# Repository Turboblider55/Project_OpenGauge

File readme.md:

<div align="center">

# 🛰️ OpenGauge

### Moduláris járműtelemetria és kijelző OBD-II-n keresztül

*Kétegységes, vezeték nélküli műszerfal valós idejű járműdiagnosztikához.*

</div>

---

*<p align="center">Illusztráció (koncepció): a jármű CAN-buszától a műszerfalra szerelhető, kerek kijelzőig.</p>*

---

## 📖 Áttekintés

Az **OpenGauge** egy BSc-szakdolgozati projekt: a jármű diagnosztikai adatainak beolvasását és megjelenítését két külön egységre bontja, amelyeket vezeték nélküli kapcsolat köt össze. Egyetlen, kijelzővel ellátott OBD-II dongle helyett két, a feladatára készült egység készül:

- **OBD-egység:** az OBD-II csatlakozóba dugott kis panel, amely a jármű CAN-buszáról olvassa a diagnosztikai adatokat, és a járműről kapja a tápfeszültségét.
- **Kijelzőegység:** a műszerfalra vagy a szellőzőrácsra szerelhető, kerek érintőkijelzős egység, amely vezeték nélkül kapja az adatokat, és animált műszereket jelenít meg. Akkumulátorról és USB-ről is működik.

A projekt része a két NYÁK megtervezése, legyártatása és üzembe helyezése, a beágyazott szoftver, a felhasználói felület és a 3D nyomtatott házak is.

A projekt nyíltan dokumentálja a tervezési hibákat is (hibanapló a `docs/` mappában), mert a felismert hibák és javításuk a fejlesztési folyamat része, és tanulságot adnak a következő verzióhoz.

---

## 🧭 Rendszerfelépítés

```
┌────────────────────────┐
│     JÁRMŰ (ECU-k)      │
│   CAN-H / CAN-L busz   │
└──────────┬─────────────┘
           │  OBD-II (J1962), ISO 15765-4
           ▼
┌────────────────────────────────────────────┐
│              OBD-EGYSÉG                    │
│  ESP32-C3-WROOM-02                         │
│  CAN-illesztő (SN65HVD23x), TWAI           │
│  Buck-áramkör (TPS54302): 12 V → 3,3 V     │
│  Bemeneti védelem (D8 SS34, D4 SMAJ24A)    │
└────────────────────┬───────────────────────┘
                     │  ESP-NOW (2,4 GHz, fix csatorna)
                     ▼
┌────────────────────────────────────────────────────┐
│              KIJELZŐEGYSÉG                         │
│  ESP32-S3-WROOM-1-N8R8 (8 MB PSRAM)                │
│  LVGL 9, QSPI kijelző-meghajtás                    │
│  Waveshare 1,85" kerek kijelző (ST77916, 360×360)  │
│  Érintő: CST816S (I²C)                             │
│  Táp: USB-C + 1S LiPo (TP4056, tápútválasztás)     │
└────────────────────────────────────────────────────┘
```

---

## ✨ Főbb jellemzők

**Hardver**
- Két egyedi, négyrétegű NYÁK (JLCPCB gyártás és szerelés).
- OBD-egység: szinkron buck, fordított polaritás elleni védelem, TVS, CAN-illesztő, ESP32-C3 modul, natív USB.
- Kijelzőegység: ESP32-S3 PSRAM-mal, USB-C és LiPo táp, töltő és tápútválasztás, 3,3 V-os LDO.

**Szoftver**
- OBD-II Mode 01 PID-ek ciklikus lekérdezése (fordulatszám, sebesség, hűtővíz, fojtószelep, akkumulátorfeszültség), a protokoll automatikus felismerésével (250/500 kbit/s, 11/29 bites azonosító).
- Többkeretes (ISO-TP) válaszok kezelése, VIN-lekérdezés.
- ESP-NOW telemetria egyszerű, verziózott bináris csomagokkal és sorszám-ellenőrzéssel.
- LVGL-alapú kerek műszerfal, folyamatos mutatómozgás a ritkább mérési adatok között.

**Opcionális bővítések**
- Alvó üzemmód, gyújtásra ébredéssel.
- BLE: médiavezérlés iOS-en (Apple Media Service) és Androidon (HID).
- Hibakódok **olvasása**.

---

## 📁 Tárolószerkezet

```
OpenGauge/
├── hardware/               # KiCad-projektek, gyártófájlok, BOM
├── firmware/
│   ├── components/         # közös komponensek (og_protocol, og_obd, og_common)
│   ├── obd_node/           # OBD-egység (ESP32-C3)
│   ├── display_node/       # kijelzőegység (ESP32-S3)
│   └── tools/
│       ├── ecu_sim/        # ESP32-S2: tesztadó és ECU-szimulátor
│       └── host_test/      # PC-s egységtesztek
├── mechanical/             # 3D nyomtatott házak (STEP/STL)
├── docs/
│   ├── fejlesztesi_naplo.xlsx   # hibák, változtatások, tervezési döntések
│   ├── 00_kepek/
│   ├── 01_projekt_bemutatas/
│   ├── 02_szoftver/
│   └── 03_hardver/
├── LICENSE
└── README.md
```

A lábkiosztások, alkatrészlisták és méretezések a `docs/03_hardver/` mappában vannak, egyetlen helyen, hogy ne legyen ellentmondás a dokumentumok között.

---

## 🛠️ Első lépések

**Előfeltételek**
- [ESP-IDF](https://docs.espressif.com/projects/esp-idf/en/latest/esp32/get-started/) 5.x (Windowson ESP-IDF Tools Installer vagy a VS Code Espressif-bővítmény)
- [KiCad](https://www.kicad.org/) a hardvertervek megnyitásához
- CMake és C++ fordító a PC-s tesztekhez

**PC-s tesztek (ESP-IDF nélkül)**
```bash
cd firmware
cmake -S tools/host_test -B build_host
cmake --build build_host
ctest --test-dir build_host --output-on-failure
```

**Fordítás és feltöltés**
```bash
# OBD-egység (ESP32-C3)
cd firmware/obd_node
idf.py set-target esp32c3
idf.py -p COM5 flash monitor

# Kijelzőegység (ESP32-S3)
cd ../display_node
idf.py set-target esp32s3
idf.py -p COM7 flash monitor
```
Két panel naplója egyszerre is figyelhető: mindkettő külön soros porton jelenik meg, külön terminálokból.

---

## 📜 Licenc és felelősségkizárás

A projekt **MIT licenc** alatt áll, a részletek a [`LICENSE`](LICENSE) fájlban találhatók.

> ⚠️ **Gépjárművi biztonsági figyelmeztetés**
> Az OpenGauge **csak olvasó** diagnosztikai eszköz. Kizárólag szabványos OBD-II diagnosztikai kéréseket küld (olvasó szolgáltatások: Mode 01 és Mode 09, tervezetten Mode 03), a válaszokat megjeleníti, de **nem ír, nem töröl és nem módosít** semmit a járműben: nem törli a hibakódokat, nem küld vezérlő- vagy beavatkozó keretet. Oktatási és diagnosztikai megjelenítési célra készült, **nem** tanúsított gépjárművi biztonsági, kibocsátás-ellenőrző vagy vezérlőeszköz. A használat saját felelősségre történik, a szerzők nem vállalnak felelősséget a jármű meghibásodásáért, elektromos károkért vagy balesetekért. Járműre csatlakoztatás előtt győződj meg a megfelelő védelemről és az OBD-II csatlakozó szabályos használatáról.

---

<div align="center">

**OpenGauge**: BSc-szakdolgozati projekt.

</div>

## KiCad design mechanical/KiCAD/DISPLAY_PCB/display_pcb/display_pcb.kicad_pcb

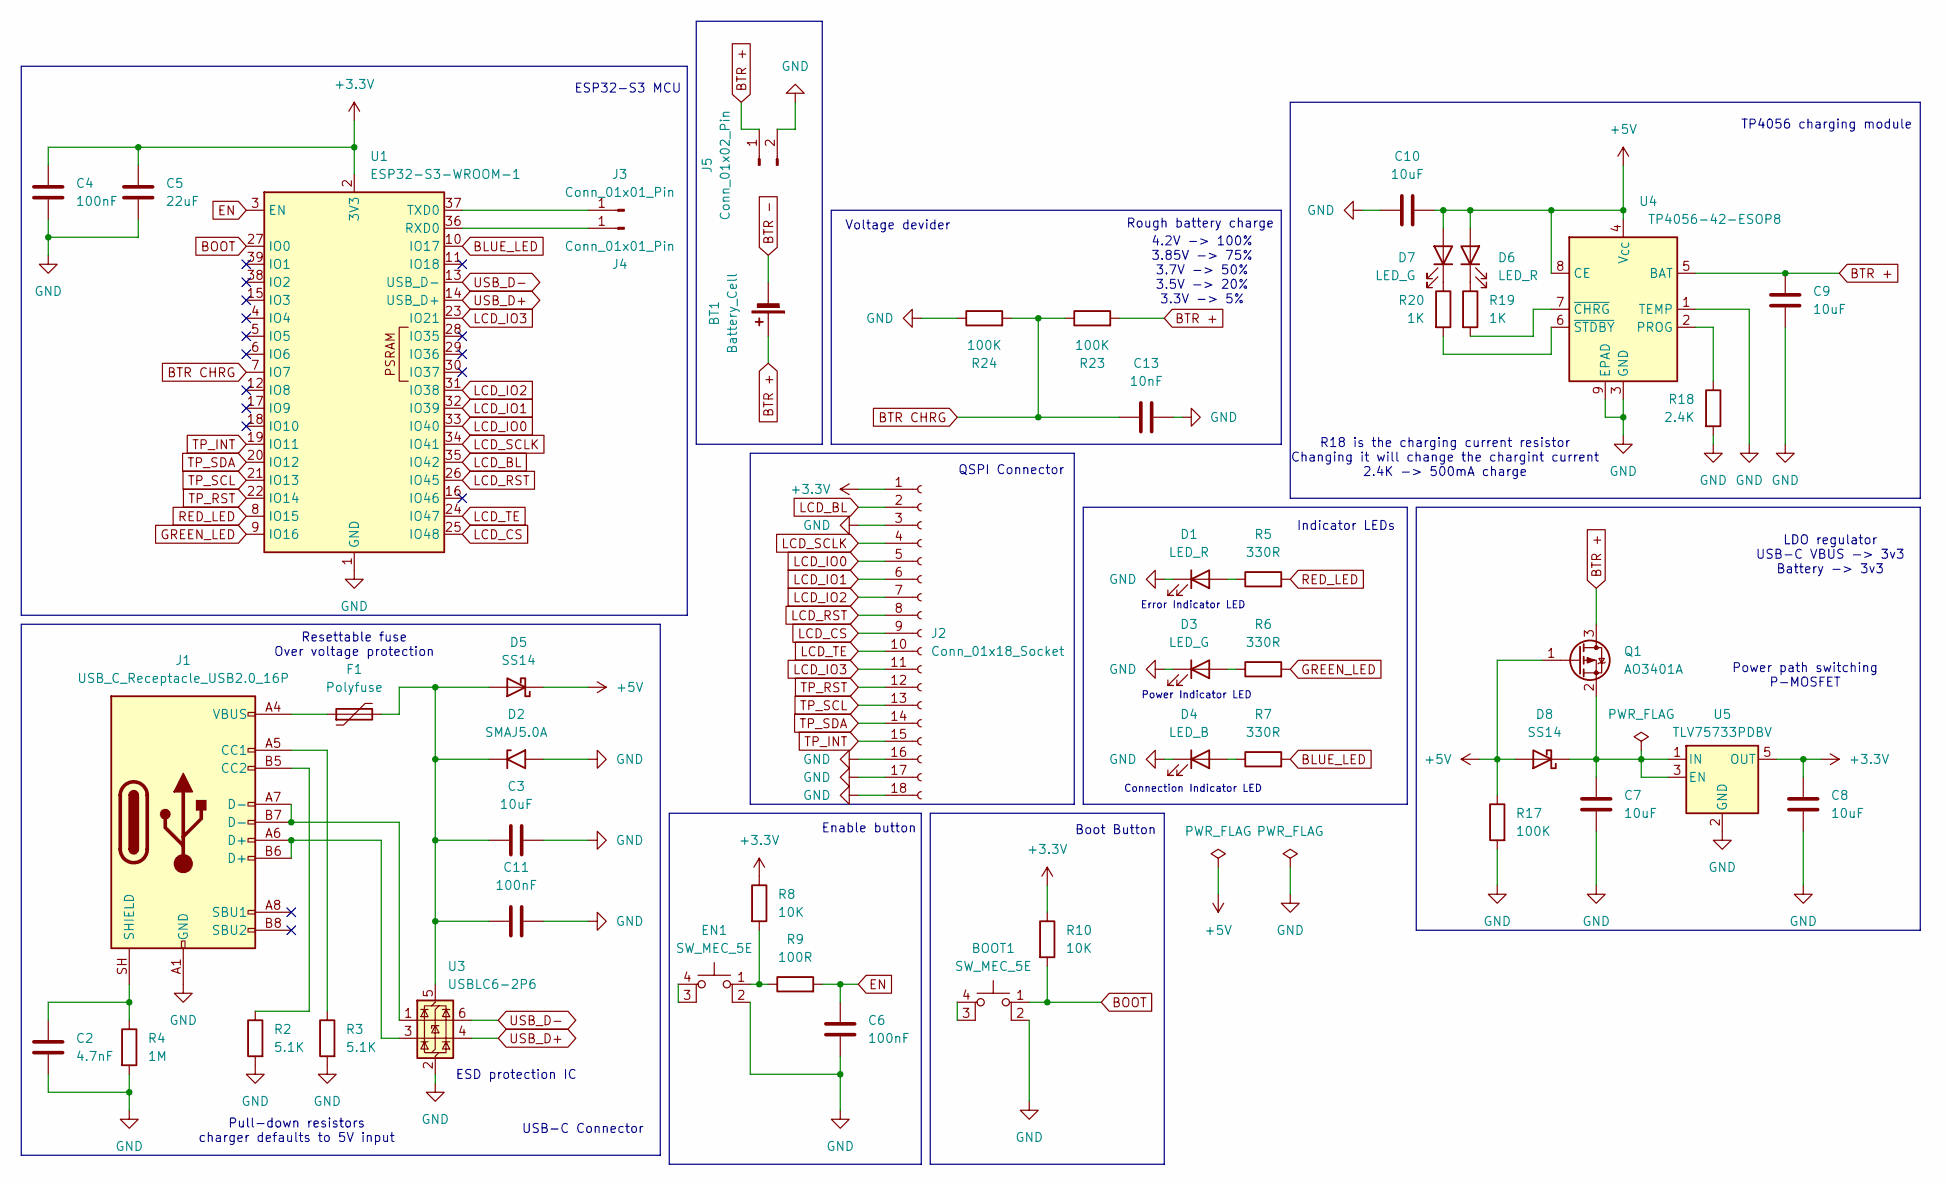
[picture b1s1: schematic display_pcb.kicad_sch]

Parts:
BOOT1: SW_MEC_5E; SW_SPST_EVQP2_MiddlePushTravel_H2.5mm; LCSC C713480
BT1: Battery_Cell
C2: 4.7nF; C_0805_2012Metric; LCSC C50131
C3, C7, C8, C9, C10: 10uF; C_1206_3216Metric; LCSC C14860
C4, C6, C11: 100nF; C_0805_2012Metric; LCSC C1711
C5: 22uF; C_1206_3216Metric; LCSC C87996
C13: 10nF; C_0805_2012Metric; LCSC C1710
D1, D6: LED_R; LED_0805_2012Metric_Pad1.15x1.40mm_HandSolder; LCSC C84256
D2: SMAJ5.0A; D_SMA; LCSC C78401
D3, D7: LED_G; LED_0805_2012Metric_Pad1.15x1.40mm_HandSolder; LCSC C2297
D4: LED_B; LED_0805_2012Metric_Pad1.15x1.40mm_HandSolder; LCSC C2293
D5, D8: SS14; D_SMA; LCSC C2480
EN1: SW_MEC_5E; SW_SPST_EVQP2_MiddlePushTravel_H2.5mm; LCSC C713480
F1: Polyfuse; Fuse_0805_2012Metric; LCSC C269104
J1: USB_C_Receptacle_USB2.0_16P; USB_C_Receptacle_GCT_USB4105-xx-A_16P_TopMnt_Horizontal; LCSC C165948
J2: Conn_01x18_Socket; Hirose_FH12-18S-0.5SH_1x18-1MP_P0.50mm_Horizontal; LCSC C506792
J3, J4: Conn_01x01_Pin; TestPoint_Pad_3.0x3.0mm
J5: Conn_01x02_Pin; Molex_PicoBlade_53261-0271_1x02-1MP_P1.25mm_Horizontal; LCSC C177225
Q1: AO3401A; SOT-23; LCSC C15127
R2, R3: 5.1K; R_0805_2012Metric; LCSC C27834
R4: 1M; R_1206_3216Metric; LCSC C17927
R5, R6, R7: 330R; R_0603_1608Metric; LCSC C23138
R8, R10: 10K; R_0805_2012Metric; LCSC C17414
R9: 100R; R_0603_1608Metric; LCSC C22775
R17, R23, R24: 100K; R_0805_2012Metric; LCSC C25611
R18: 2.4K; R_0805_2012Metric; LCSC C17526
R19, R20: 1K; R_0805_2012Metric; LCSC C17513
U1: ESP32-S3-WROOM-1; LCSC C2913201
U3: USBLC6-2P6; SOT-666; LCSC C2827693
U4: TP4056-42-ESOP8; SOIC-8-1EP_3.9x4.9mm_P1.27mm_EP2.41x3.3mm_ThermalVias; LCSC C16581
U5: TLV75733PDBV; SOT-23-5; LCSC C485517

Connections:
+3.3V: C4.1, C5.1, C8.1, J2.1, R8.1, R10.1, U1.2 (3V3), U5.5 (OUT)
+5V: C10.2, D5.1 (K), D6.2 (A), D7.2 (A), D8.2 (A), Q1.1 (G), R17.1, U4.4 (V_{CC}), U4.8 (CE)
BLUE_LED: R7.2, U1.10 (IO17)
BOOT: BOOT1.1, R10.2, U1.27 (IO0)
BTR +: BT1.1 (+), C9.1, J5.1, Q1.3 (D), R23.2, U4.5 (BAT)
BTR CHRG: C13.1, R23.1, R24.2, U1.7 (IO7)
EN: C6.2, R9.2, U1.3 (EN)
GND: BOOT1.2, C2.2, C3.1, C4.2, C5.2, C6.1, C7.2, C8.2, C9.2, C10.1, C11.1, C13.2, D1.1 (K), D2.2 (A2), D3.1 (K), D4.1 (K), EN1.2, J1.A1 (GND), J1.A12 (GND), J1.B1 (GND), J1.B12 (GND), J2.3, J2.16, J2.17, J2.18, J5.2, R2.2, R3.2, R4.2, R17.2, R18.2, R24.1, U1.1 (GND), U1.40 (GND), U1.41 (GND), U3.2 (GND), U4.1 (TEMP), U4.3 (GND), U4.9 (EPAD), U5.2 (GND)
GREEN_LED: R6.2, U1.9 (IO16)
LCD_BL: J2.2, U1.35 (IO42)
LCD_CS: J2.9, U1.25 (IO48)
LCD_IO0: J2.5, U1.33 (IO40)
LCD_IO1: J2.6, U1.32 (IO39)
LCD_IO2: J2.7, U1.31 (IO38)
LCD_IO3: J2.11, U1.23 (IO21)
LCD_RST: J2.8, U1.26 (IO45)
LCD_SCLK: J2.4, U1.34 (IO41)
LCD_TE: J2.10, U1.24 (IO47)
unnamed: D1.2 (A), R5.1
unnamed: C3.2, C11.2, D2.1 (A1), D5.2 (A), F1.2, U3.5 (VBUS)
unnamed: D3.2 (A), R6.1
unnamed: D4.2 (A), R7.1
unnamed: D6.1 (K), R19.1
unnamed: D7.1 (K), R20.1
unnamed: C7.1, D8.1 (K), Q1.2 (S), U5.1 (IN), U5.3 (EN)
unnamed: EN1.1, R8.2, R9.1
unnamed: F1.1, J1.A4 (VBUS), J1.A9 (VBUS), J1.B4 (VBUS), J1.B9 (VBUS)
unnamed: J1.A5 (CC1), R3.1
unnamed: J1.B5 (CC2), R2.1
unnamed: J1.A6 (D+), J1.B6 (D+), U3.3 (I/O2)
unnamed: J1.A7 (D-), J1.B7 (D-), U3.1 (I/O1)
unnamed: C2.1, J1.SH (SHIELD), R4.1
unnamed: J3.1 (Pin_1_1), U1.37 (TXD0)
unnamed: J4.1 (Pin_1_1), U1.36 (RXD0)
unnamed: R18.1, U4.2 (PROG)
unnamed: R19.2, U4.7 (~CHRG)
unnamed: R20.2, U4.6 (~STDBY)
RED_LED: R5.2, U1.8 (IO15)
TP_INT: J2.15, U1.19 (IO11)
TP_RST: J2.12, U1.22 (IO14)
TP_SCL: J2.13, U1.21 (IO13)
TP_SDA: J2.14, U1.20 (IO12)
USB_D+: U1.14 (USB_D+), U3.4 (I/O2)
USB_D-: U1.13 (USB_D-), U3.6 (I/O1)

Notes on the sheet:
Enable button
Power Indicator LED
Resettable fuse Over voltage protection
ESP32-S3 MCU
Error Indicator LED
4.2V -> 100% 3.85V -> 75% 3.7V -> 50% 3.5V -> 20% 3.3V -> 5%
Connection Indicator LED
Indicator LEDs
QSPI Connector
Rough battery charge
R18 is the charging current resistor Changing it will change the chargint current 2.4K -> 500mA charge
TP4056 charging module
LDO regulator USB-C VBUS -> 3v3 Battery -> 3v3
Voltage devider
Boot Button
USB-C Connector
Power path switching P-MOSFET
Pull-down resistors charger defaults to 5V input
ESD protection IC

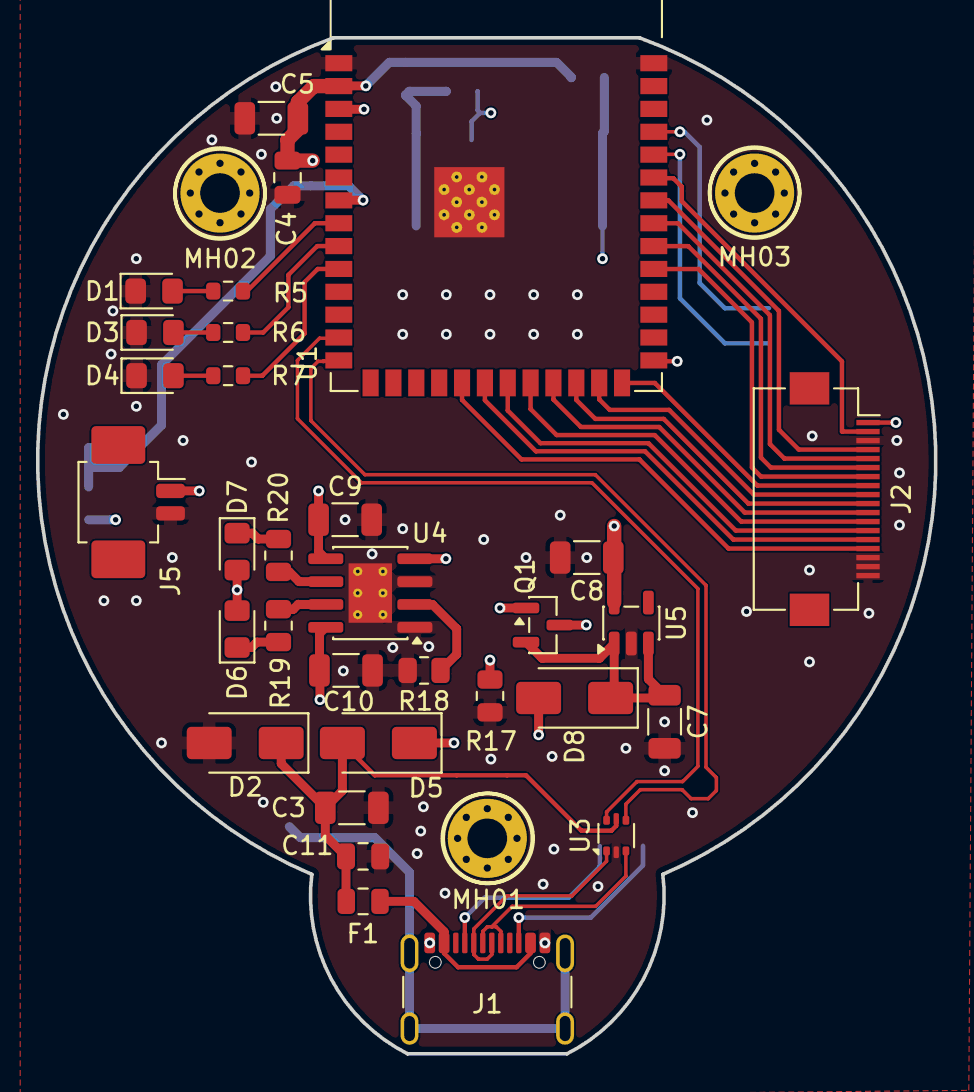
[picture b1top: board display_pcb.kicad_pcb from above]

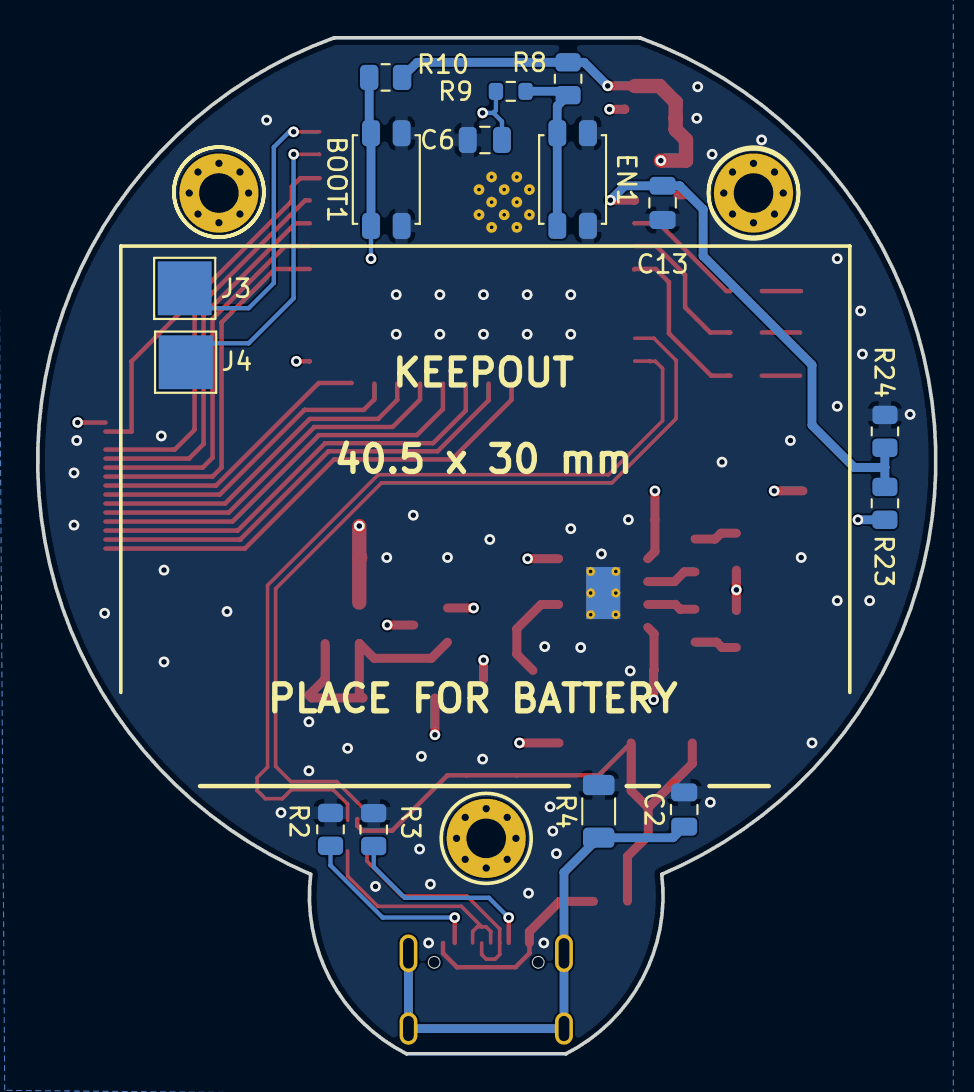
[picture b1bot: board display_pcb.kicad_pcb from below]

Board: 4 copper layers, 49.9 x 56.4 mm, 50 parts (15 on the bottom side), 44 nets.

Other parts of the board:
MH01, MH02, MH03: MountingHole_2.2mm_M2_Pad_Via

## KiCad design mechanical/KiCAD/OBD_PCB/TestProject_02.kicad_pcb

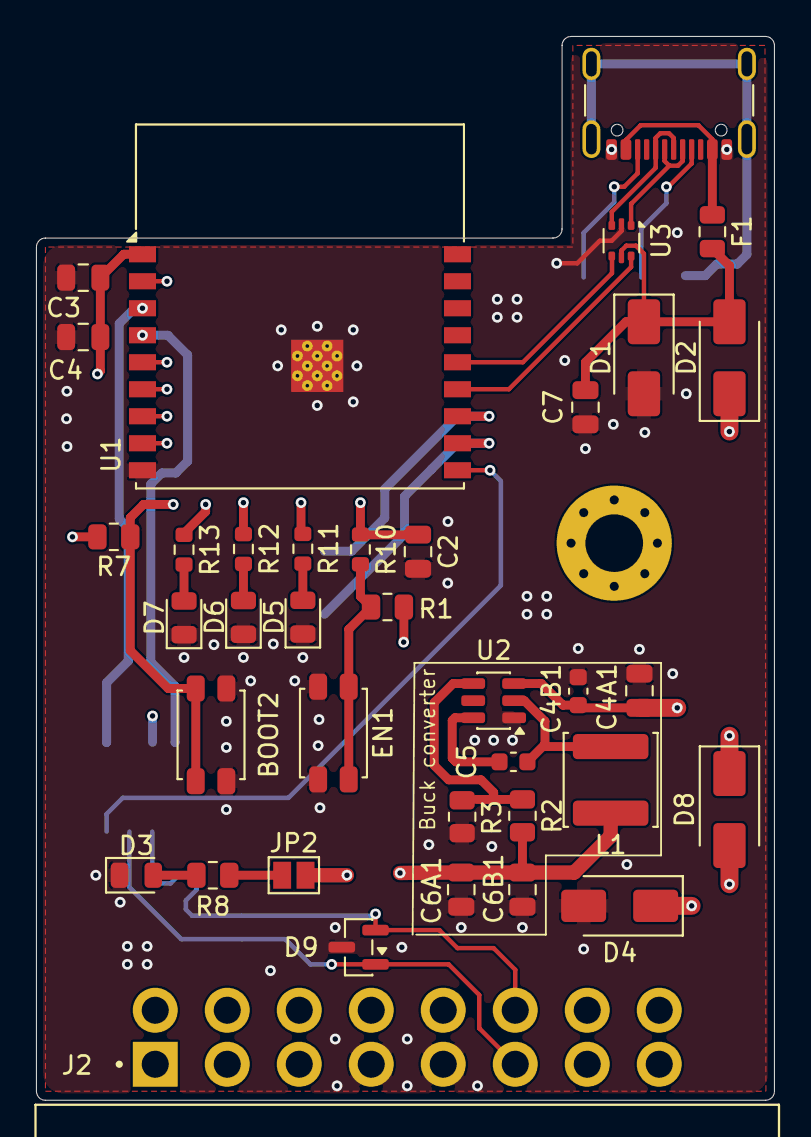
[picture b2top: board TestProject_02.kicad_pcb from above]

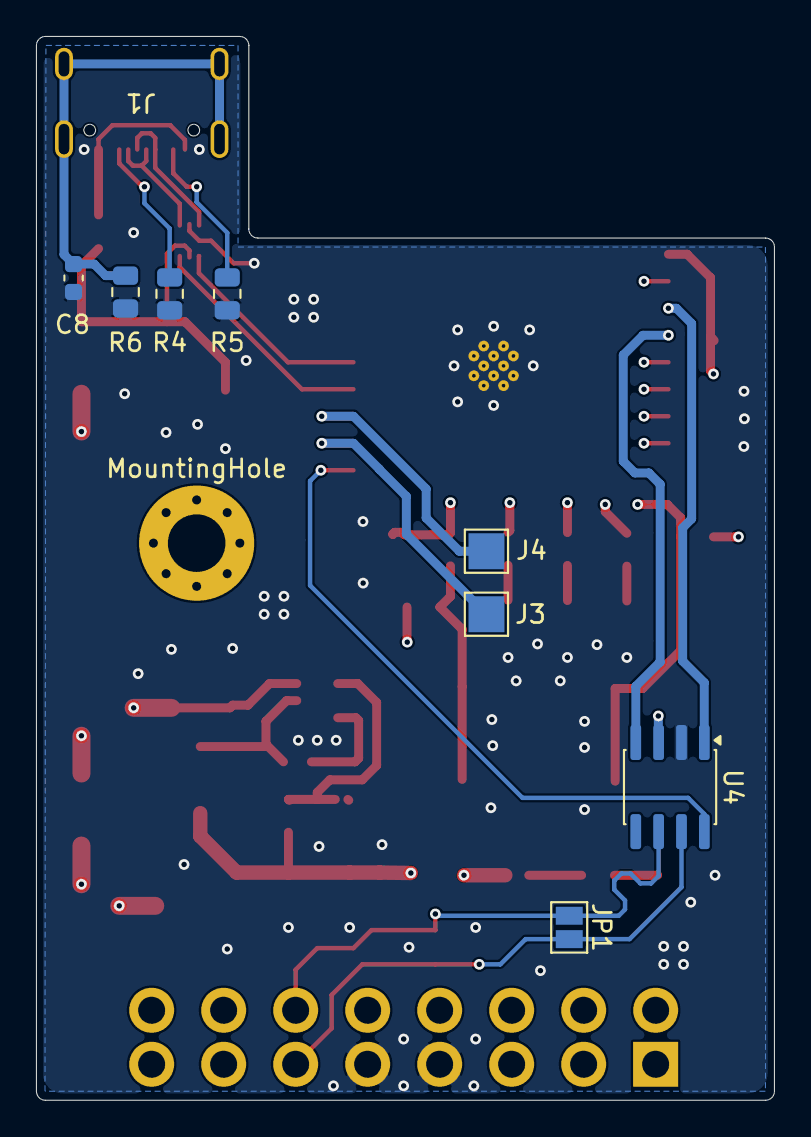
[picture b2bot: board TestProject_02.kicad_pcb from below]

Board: 4 copper layers, 41.0 x 59.1 mm, 46 parts (9 on the bottom side), 34 nets.

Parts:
BOOT2: SW_MEC_5E; SW_SPST_EVQP2_MiddlePushTravel_H2.5mm
C2, C3: 100nF; C_0805_2012Metric
C4, C4A1, C7: 10uF; C_0805_2012Metric
C4B1, C5: 100nF; C_0603_1608Metric
C6A1, C6B1: 22uF; C_0805_2012Metric
C8: 4.7nF; C_0603_1608Metric
D1: SMAJ5.0A; D_SMA
D2: SS14; D_SMA
D3, D5: LED_G; LED_0805_2012Metric
D4: SMAJ24A; D_SMA
D6: LED_B; LED_0805_2012Metric
D7: LED_R; LED_0805_2012Metric
D8: SS34; D_SMA
D9: NUP2105L; SOT-23
EN1: SW_MEC_5E; SW_SPST_EVQP2_MiddlePushTravel_H2.5mm
F1: Polyfuse; Fuse_0805_2012Metric
J1: USB_C_Receptacle_USB2.0_16P; USB_C_Receptacle_GCT_USB4105-xx-A_16P_TopMnt_Horizontal
J2: C-OBD-II-16M; COMTECH_C-OBD-II-16M
J3: TXD_PAD; TestPoint_Pad_2.0x2.0mm
J4: RXD_PAD; TestPoint_Pad_2.0x2.0mm
JP1: SolderJumper_2_Open; SolderJumper-2_P1.3mm_Open_Pad1.0x1.5mm
JP2: Power Line Tester; SolderJumper-2_P1.3mm_Open_Pad1.0x1.5mm
L1: 10uH; L_Sunlord_SWPA5040S
MountingHole: MountingHole_3.2mm_M3_Pad_Via
R1, R3, R7: 10k; R_0805_2012Metric
R2: 45.3K; R_0805_2012Metric
R4, R5: 5.1K; R_0805_2012Metric
R6: 1M; R_0805_2012Metric
R8: 1.5K; R_0805_2012Metric
R10: 100R; R_0603_1608Metric
R11, R12, R13: 330R; R_0603_1608Metric
U1: ESP32-C3-WROOM-02
U2: TPS54302; SOT-23-6
U3: USBLC6-2P6; SOT-666
U4: SN65HVD231; SOIC-8_3.9x4.9mm_P1.27mm

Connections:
+3.3V: C3.1, C4.1, C6A1.1, C6B1.1, JP2.2 (B), L1.2, R1.2, R2.2, R7.2, U1.1 (3V3), U4.3 (VCC)
/D+: J1.A6 (D+), J1.B6 (D+), U3.3 (I/O2)
/D-: J1.A7 (D-), J1.B7 (D-), U3.1 (I/O1)
BOOT: BOOT2.1, R7.1, U1.8 (IO9)
CANH: D9.1 (K), J2.6, JP1.2 (B), U4.7 (CANH)
CANL: D9.2 (K), J2.14, JP1.1 (A), U4.6 (CANL)
CAN_RX: U1.4 (IO5), U4.4 (R)
CAN_TX: U1.3 (IO4), U4.1 (D)
EN: C2.1, R10.1, U1.2 (EN)
GND: BOOT2.2, C2.2, C3.2, C4.2, C4A1.2, C4B1.2, C6A1.2, C6B1.2, C7.2, C8.1, D1.2 (A2), D3.1 (K), D4.2 (A2), D5.1 (K), D6.1 (K), D7.1 (K), D9.3 (A), EN1.2, J1.A1 (GND), J1.A12 (GND), J1.B1 (GND), J1.B12 (GND), J2.4, J2.5, R3.1, R4.2, R5.2, R6.2, U1.9 (GND), U1.19 (GND), U2.1 (GND), U3.2 (GND), U4.2 (GND)
unnamed: C7.1, D1.1 (A1), D2.2 (A), F1.2, U3.5 (VBUS)
unnamed: D3.2 (A), R8.1
unnamed: D4.1 (A1), D8.2 (A), J2.16
unnamed: D5.2 (A), R11.2
unnamed: D6.2 (A), R12.2
unnamed: D7.2 (A), R13.2
unnamed: EN1.1, R1.1, R10.2
unnamed: F1.1, J1.A4 (VBUS), J1.A9 (VBUS), J1.B4 (VBUS), J1.B9 (VBUS)
unnamed: J1.A5 (CC1), R4.1
unnamed: J1.B5 (CC2), R5.1
unnamed: C8.2, J1.SH (SHIELD), R6.1
unnamed: J3.1 (Pin_1_1), U1.11 (IO20/RXD)
unnamed: J4.1 (Pin_1_1), U1.12 (IO21/TXD)
unnamed: JP2.1 (A), R8.2
unnamed: R11.1, U1.5 (IO6)
unnamed: R12.1, U1.6 (IO7)
unnamed: R13.1, U1.7 (IO8)
unnamed: C5.1, U2.6 (BOOT)
unnamed: R2.1, R3.2, U2.4 (FB)
unnamed: C5.2, L1.1, U2.2 (SW)
OPMODE: U1.10 (IO10), U4.8 (Rs)
USB_D+: U1.14 (IO19), U3.4 (I/O2)
USB_D-: U1.13 (IO18), U3.6 (I/O1)
VIN: C4A1.1, C4B1.1, D2.1 (K), D8.1 (K), U2.3 (VIN)
